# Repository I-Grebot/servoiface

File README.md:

# servoiface

DC Servo motor interface

Board use to control a DC motor and act as a servomotor, based on STM32F042 MCU. 

Position feedback can be provided by potentiometer, limit switches or encoder. 

Reference position command can be provided from a PWM signal such as regular RC servomotors, or an halfduplex UART such as Dynamixel smart servomotors.

Motor current limitation can be driven, thus the device can be used as a torque controlled system (useful for robot gripper, for instance).

Debug RGB, tactile switch, and potentiometer can be used for system calibration and visual feedback.

Board:

Schematics:

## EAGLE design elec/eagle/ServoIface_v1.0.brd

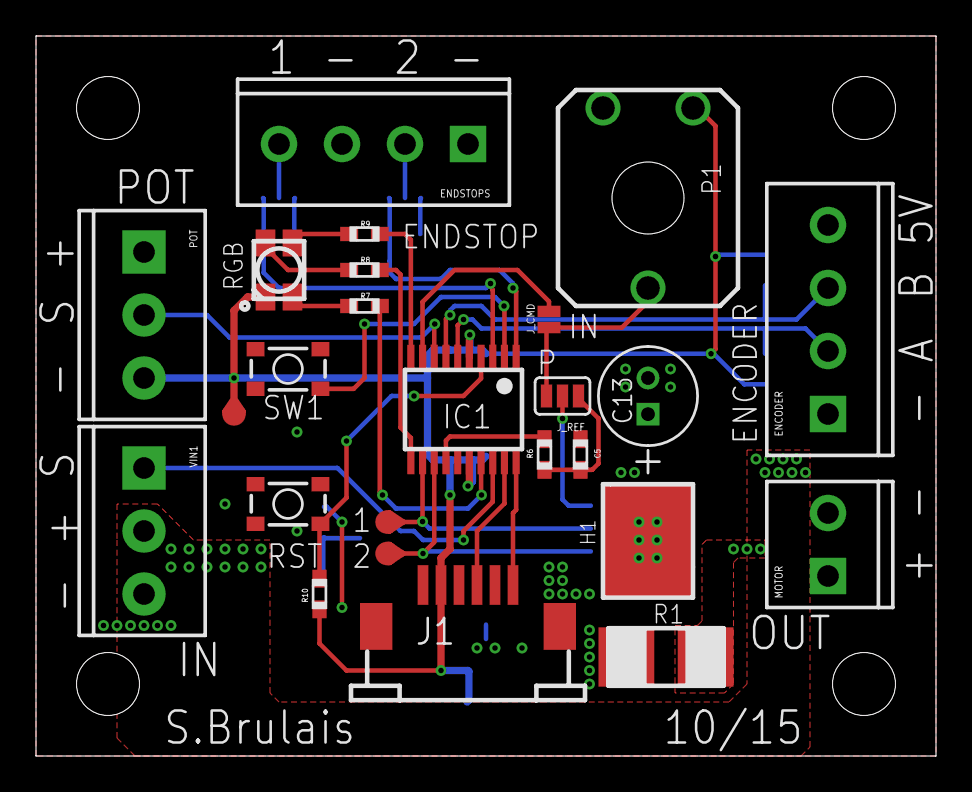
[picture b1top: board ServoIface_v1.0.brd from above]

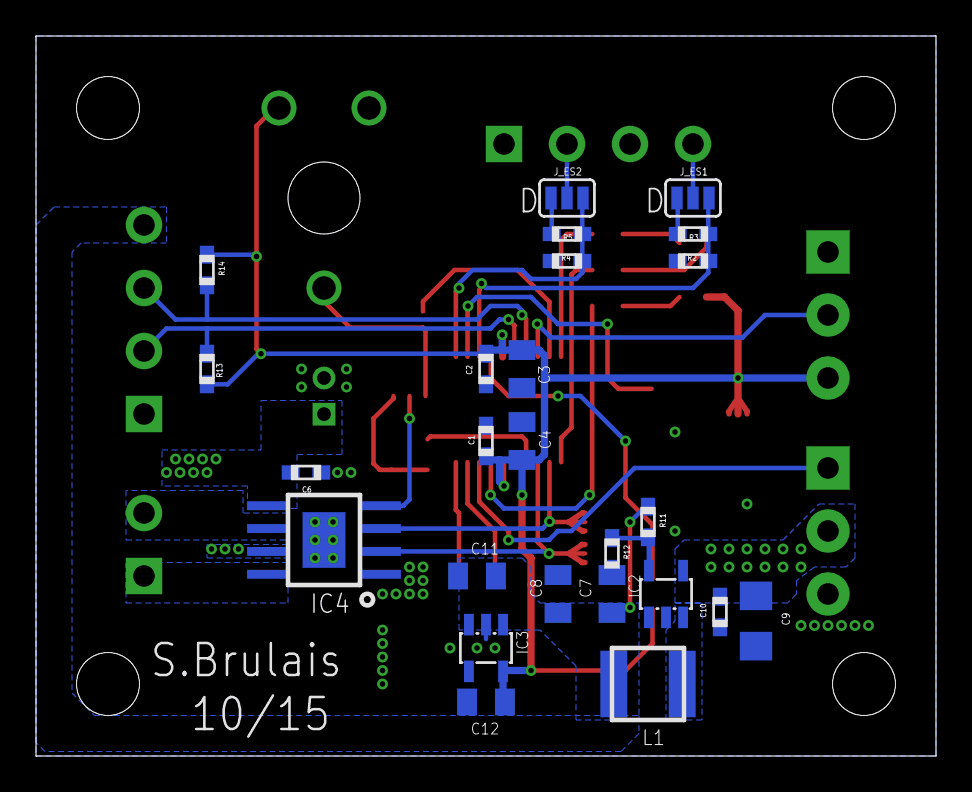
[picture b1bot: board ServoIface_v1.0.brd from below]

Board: 2 copper layers, 50.0 x 40.0 mm, 50 parts (25 on the bottom side), 36 nets.

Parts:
C1, C6, C10: 100nF; R0603
C2: 10nF; R0603
C3, C11: 1uF; R0805
C4: 4.7uF; R0805
C5: 470nF; R0603
C7, C8: 10uF; R0805
C9: 10uF; 1206
C12: 2.2uF; R0805
C13: 47UF; CAPPR200-500X1600
ENCODER: SCREWTERMINAL-3.5MM-4
ENDSTOPS: SCREWTERMINAL-3.5MM-4
H1: HEAT_SINK; HEAT_A5_SA
IC1: STM32F042; TSSOP20
IC2: TPS560200; SOT23-5L
IC3: LP2980; SOT23-5L
IC4: DRV8870; HSOP_8P
J1: J_SWD; ZIF-06-1MM
J_CMD: PAD-JUMPER-2-NO_NO_SILK
J_ES1, J_ES2: SJ_3
J_REF: SJ_3
L1: NRG_4026
MOTOR: M023.5MM; SCREWTERMINAL-3.5MM-2
P1: TRIMPOTCB10; POT_CB10
POT: SCREWTERMINAL-3.5MM-3
R1: 0.15; CRF2512
R2, R4, R10: 4.7k; R0603
R3, R5, R7, R8, R9: R0603
R6: 330k; R0603
R11: 105k; R0603
R12: 20k; R0603
R13, R14: NC; R0603
RGB: LED-TRICOLOR; PLCC4
S1: TACTILE_SWITCH_SMD-3
S_RST: TACTILE_SWITCH_SMD-3
TP1, TP2, TP3: TEST_POINT_R04; TP_R04
VIN1: SCREWTERMINAL-3.5MM-3

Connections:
3.3V: C1.2, C2.2, C3.2, C4.2, C12.2, IC1.P$5, IC1.P$16, IC3.5, J1.2, P1.P$1, POT.3, R10.2, R13.2, R14.2, RGB.P$1, TP3.P$1
5V: C7.2, C8.2, C11.2, ENCODER.4, IC3.1, IC3.3, L1.P$2, R11.2
CMD_ANALOG: IC1.P$9, J_CMD.1
CMD_IN: IC1.P$18, VIN1.1
ENC_A: ENCODER.2, IC1.P$6, R13.1
ENC_B: ENCODER.3, IC1.P$7, R14.1
ENDSTOP_1: IC1.P$3, J_ES1.3, R2.2, R3.1
ENDSTOP_2: IC1.P$1, J_ES2.3, R4.2, R5.1
GND: C1.1, C2.1, C3.1, C4.1, C5.1, C6.1, C7.1, C8.1, C9.1, C10.1, C11.1, C12.1, C13.2, ENCODER.1, ENDSTOPS.1, ENDSTOPS.3, H1.P$1, IC1.P$15, IC2.2, IC3.2, IC4.P$1, IC4.PAD, J1.1, J1.3, J1.5, P1.P$2, POT.1, R1.P$1, R2.1, R4.1, R12.1, S1.1, S_RST.1, VIN1.3
LED_B: IC1.P$11, R8.1
LED_G: IC1.P$10, R9.1
LED_R: IC1.P$17, R7.1
MOT+: IC4.P$8, MOTOR.1
MOT-: IC4.P$6, MOTOR.2
MOTOR_CUR_REF: IC1.P$14, R6.1
MOTOR_IN1: IC1.P$12, IC4.P$3, TP1.P$1
MOTOR_IN2: IC1.P$13, IC4.P$2, TP2.P$1
MOTOR_VREF: IC4.P$4, J_REF.2
unnamed: IC4.P$7, R1.P$2
unnamed: ENDSTOPS.2, J_ES2.2
unnamed: J_ES2.1, R5.2
unnamed: ENDSTOPS.4, J_ES1.2
unnamed: J_ES1.1, R3.2
unnamed: J_CMD.2, J_REF.3, P1.P$3
unnamed: C5.2, J_REF.1, R6.2
unnamed: R7.2, RGB.P$4
unnamed: R8.2, RGB.P$2
unnamed: R9.2, RGB.P$3
unnamed: IC1.P$4, R10.1, S_RST.4
unnamed: IC2.3, L1.P$1
unnamed: IC2.5, R11.1, R12.2
POT_IN: IC1.P$8, POT.2
SW1: IC1.P$2, S1.4
SWCLK: IC1.P$20, J1.6
SWDIO: IC1.P$19, J1.4
VCC: C6.2, C9.2, C10.2, C13.1, IC2.4, IC4.P$5, VIN1.2

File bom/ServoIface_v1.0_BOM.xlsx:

Cmd | Qty | Value | Device | Package | Parts | Description
 | 3 |  | JUMPER-3SMD | SJ_3 | J_ES1, J_ES2, J_REF
 | 1 |  | JUMPER-PAD-2-NO | PAD-JUMPER-2-NO_NO_SILK | J_CMD
 | 1 |  | LNRG_4026 | NRG_4026 | L1
 | 2 |  | M03SCREW | SCREWTERMINAL-3.5MM-3 | POT, VIN1 | Header 3
 | 2 |  | M04SCREW | SCREWTERMINAL-3.5MM-4 | ENCODER, ENDSTOPS | Header 4
 | 5 |  | R0603 | R0603 | R3, R5, R7, R8, R9
 | 2 |  | SWITCH-MOMENTARY-2SMD-3 | TACTILE_SWITCH_SMD-3 | S1, S_RST | Various NO switches- pushbuttons, reed, etc
 | 1 | 47UF | C_PANAFM1E470-P2.0 | CAPPR200-500X1600 | C13 | Aluminum Electrolytic Capacitors
 | 1 | 0.15 | R2512 | CRF2512 | R1
 | 3 | 100nF | C0603 | R0603 | C1, C6, C10
 | 1 | 105k | R0603 | R0603 | R11
 | 1 | 10nF | C0603 | R0603 | C2
 | 2 | 10uF | C0805 | R0805 | C7, C8
 | 1 | 10uF | C1206 | 1206 | C9
 | 2 | 1uF | C0805 | R0805 | C3, C11
 | 1 | 2.2uF | C0805 | R0805 | C12
 | 1 | 20k | R0603 | R0603 | R12
 | 1 | 330k | R0603 | R0603 | R6
 | 3 | 4.7k | R0603 | R0603 | R2, R4, R10
 | 1 | 4.7uF | C0805 | R0805 | C4
 | 1 | 470nF | C0603 | R0603 | C5
 | 1 | DRV8870 | DRV8870 | HSOP_8P | IC4 | DRV8870 3.6-A Brushed DC Motor Driver (PWM Control)
 | 1 | HEAT_SINK | HEAT_SINK | HEAT_A5_SA | H1 | ICK SMD A 5 SA Farnell 4302163
 | 1 | J_SWD | ZIF-06-1MM | ZIF-06-1MM | J1
 | 1 | LED-TRICOLOR | LED-TRICOLOR | PLCC4 | RGB | Tri-Color LED SMD
 | 1 | LP2980 | LP2980 | SOT23-5L | IC3
 | 1 | M023.5MM | M023.5MM | SCREWTERMINAL-3.5MM-2 | MOTOR | Standard 2-pin 0.1 header. Use with"
 | 2 | NC | R0603 | R0603 | R13, R14
 | 1 | STM32F042 | STM32F042 | TSSOP20 | IC1 | ARM®-based 32-bit MCU, up to 32 KB Flash, crystal-less USB
 | 3 | TEST_POINT_R04 | TEST_POINT_R04 | TP_R04 | TP1, TP2, TP3
Ti | 1 | TPS560200 | TPS560200 | SOT23-5L | IC2
 | 1 | TRIMPOTCB10 | TRIMPOTCB10 | POT_CB10 | P1 | Various small potentiometers for set-and-forget" applications"

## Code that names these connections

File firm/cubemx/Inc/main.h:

/**
  ******************************************************************************
  * File Name          : main.h
  * Description        : This file contains the common defines of the application
  ******************************************************************************
  *
  * Copyright (c) 2017 STMicroelectronics International N.V. 
  * All rights reserved.
  *
  * Redistribution and use in source and binary forms, with or without 
  * modification, are permitted, provided that the following conditions are met:
  *
  * 1. Redistribution of source code must retain the above copyright notice, 
  *    this list of conditions and the following disclaimer.
  * 2. Redistributions in binary form must reproduce the above copyright notice,
  *    this list of conditions and the following disclaimer in the documentation
  *    and/or other materials provided with the distribution.
  * 3. Neither the name of STMicroelectronics nor the names of other 
  *    contributors to this software may be used to endorse or promote products 
  *    derived from this software without specific written permission.
  * 4. This software, including modifications and/or derivative works of this 
  *    software, must execute solely and exclusively on microcontroller or
  *    microprocessor devices manufactured by or for STMicroelectronics.
  * 5. Redistribution and use of this software other than as permitted under 
  *    this license is void and will automatically terminate your rights under 
  *    this license. 
  *
  * THIS SOFTWARE IS PROVIDED BY STMICROELECTRONICS AND CONTRIBUTORS "AS IS" 
  * AND ANY EXPRESS, IMPLIED OR STATUTORY WARRANTIES, INCLUDING, BUT NOT 
  * LIMITED TO, THE IMPLIED WARRANTIES OF MERCHANTABILITY, FITNESS FOR A 
  * PARTICULAR PURPOSE AND NON-INFRINGEMENT OF THIRD PARTY INTELLECTUAL PROPERTY
  * RIGHTS ARE DISCLAIMED TO THE FULLEST EXTENT PERMITTED BY LAW. IN NO EVENT 
  * SHALL STMICROELECTRONICS OR CONTRIBUTORS BE LIABLE FOR ANY DIRECT, INDIRECT,
  * INCIDENTAL, SPECIAL, EXEMPLARY, OR CONSEQUENTIAL DAMAGES (INCLUDING, BUT NOT
  * LIMITED TO, PROCUREMENT OF SUBSTITUTE GOODS OR SERVICES; LOSS OF USE, DATA, 
  * OR PROFITS; OR BUSINESS INTERRUPTION) HOWEVER CAUSED AND ON ANY THEORY OF 
  * LIABILITY, WHETHER IN CONTRACT, STRICT LIABILITY, OR TORT (INCLUDING 
  * NEGLIGENCE OR OTHERWISE) ARISING IN ANY WAY OUT OF THE USE OF THIS SOFTWARE,
  * EVEN IF ADVISED OF THE POSSIBILITY OF SUCH DAMAGE.
  *
  ******************************************************************************
  */
/* Define to prevent recursive inclusion -------------------------------------*/
#ifndef __MAIN_H
#define __MAIN_H
  /* Includes ------------------------------------------------------------------*/

#include <stdint.h>
#include <stdbool.h>

/* USER CODE BEGIN Includes */

/* USER CODE END Includes */

/* Private define ------------------------------------------------------------*/

#define ENDSTOP_2_Pin GPIO_PIN_8
#define ENDSTOP_2_GPIO_Port GPIOB
#define SW1_Pin GPIO_PIN_0
#define SW1_GPIO_Port GPIOF
#define ENDSTOP_1_Pin GPIO_PIN_1
#define ENDSTOP_1_GPIO_Port GPIOF
#define ENC_A_Pin GPIO_PIN_0
#define ENC_A_GPIO_Port GPIOA
#define ENC_B_Pin GPIO_PIN_1
#define ENC_B_GPIO_Port GPIOA
#define POT_IN_Pin GPIO_PIN_2
#define POT_IN_GPIO_Port GPIOA
#define CMD_ANALOG_Pin GPIO_PIN_3
#define CMD_ANALOG_GPIO_Port GPIOA
#define LED_G_Pin GPIO_PIN_4
#define LED_G_GPIO_Port GPIOA
#define LED_B_Pin GPIO_PIN_5
#define LED_B_GPIO_Port GPIOA
#define MOT_IN1_Pin GPIO_PIN_6
#define MOT_IN1_GPIO_Port GPIOA
#define MOT_IN2_Pin GPIO_PIN_7
#define MOT_IN2_GPIO_Port GPIOA
#define MOT_CUR_Pin GPIO_PIN_1
#define MOT_CUR_GPIO_Port GPIOB
#define LED_R_Pin GPIO_PIN_9
#define LED_R_GPIO_Port GPIOA
#define CMD_IN_Pin GPIO_PIN_10
#define CMD_IN_GPIO_Port GPIOA

// Macros

#define LEDR_WR(_v) {HAL_GPIO_WritePin(GPIOA, LED_R_Pin, (_v));}
#define LEDG_WR(_v) {HAL_GPIO_WritePin(GPIOA, LED_G_Pin, (_v));}
#define LEDB_WR(_v) {HAL_GPIO_WritePin(GPIOA, LED_B_Pin, (_v));}

// Leds
#define LEDx_ON   GPIO_PIN_RESET
#define LEDx_OFF  GPIO_PIN_SET

#define LED_WHITE   {LEDR_WR(LEDx_ON);  LEDG_WR(LEDx_ON);   LEDB_WR(LEDx_ON) ;}
#define LED_RED     {LEDR_WR(LEDx_ON);  LEDG_WR(LEDx_OFF);  LEDB_WR(LEDx_OFF);}
#define LED_GREEN   {LEDR_WR(LEDx_OFF); LEDG_WR(LEDx_ON);   LEDB_WR(LEDx_OFF);}
#define LED_BLUE    {LEDR_WR(LEDx_OFF); LEDG_WR(LEDx_OFF);  LEDB_WR(LEDx_ON) ;}
#define LED_CYAN    {LEDR_WR(LEDx_OFF); LEDG_WR(LEDx_ON);   LEDB_WR(LEDx_ON) ;}
#define LED_YELLOW  {LEDR_WR(LEDx_ON);  LEDG_WR(LEDx_ON);   LEDB_WR(LEDx_OFF);}
#define LED_MAGENTA {LEDR_WR(LEDx_ON);  LEDG_WR(LEDx_OFF);  LEDB_WR(LEDx_ON) ;}
#define LED_OFF     {LEDR_WR(LEDx_OFF); LEDG_WR(LEDx_OFF);  LEDB_WR(LEDx_OFF);}

// Commands
#define CMD_WAIT          0U
#define CMD_SHOOT_HIGH    2U
#define CMD_SHOOT_LOW     3U
#define CMD_INIT          1U

// Objective positions
#define POS_RESET     100
#define POS_ONE_TURN  8000

// Objective speeds
#define SPEED_FAST  1023
#define SPEED_SLOW  300
#define SPEED_INIT -200

/* USER CODE BEGIN Private defines */

uint8_t HwGetCommand(void);

/* USER CODE END Private defines */

/**
  * @}
  */ 

/**
  * @}
*/ 

#endif /* __MAIN_H */
/************************ (C) COPYRIGHT STMicroelectronics *****END OF FILE****/

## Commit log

2016-11-24 Added Eagle files
2016-11-24 Adde dxf file for mecanichal purposes
2016-11-24 Added project's bill of material
2016-12-16 Folder organizing, elec and firm
2017-03-14 WIP: generated TrueStudio project
2017-03-15 WIP: GPIO OK, ENCODER IN PROGRESS
2017-03-16 WIP: demo maker-faire without encoder
2017-03-18 WIP: demo maker-faire without encoder j2
2017-04-02 Encoders ok
2017-05-13 Moved the SeroIface logic into a dedicated file.
2017-05-21 JST pas de capture event
2017-05-27 Final code with 2x GPIO input controls
2017-10-23 Branche 2018
2017-10-26 Adde PID library, not tested
2017-10-26 Added PID library, not tested
2017-10-26 Revert "Added PID library, not tested"
    This reverts commit 83dac406912ce2a4daf5a567a052a64a8f02eda2.
2017-10-27 feature PID validated
2017-10-27 Bakup file removed
2018-05-10 2 speed control working
2018-05-14 2nd speed is slower, and init default

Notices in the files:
parts and their libraries:
SparkFun-Connectors: Licensing: Creative Commons ShareAlike 4.0 International - https://creativecommons.org/licenses/by-sa/4.0
